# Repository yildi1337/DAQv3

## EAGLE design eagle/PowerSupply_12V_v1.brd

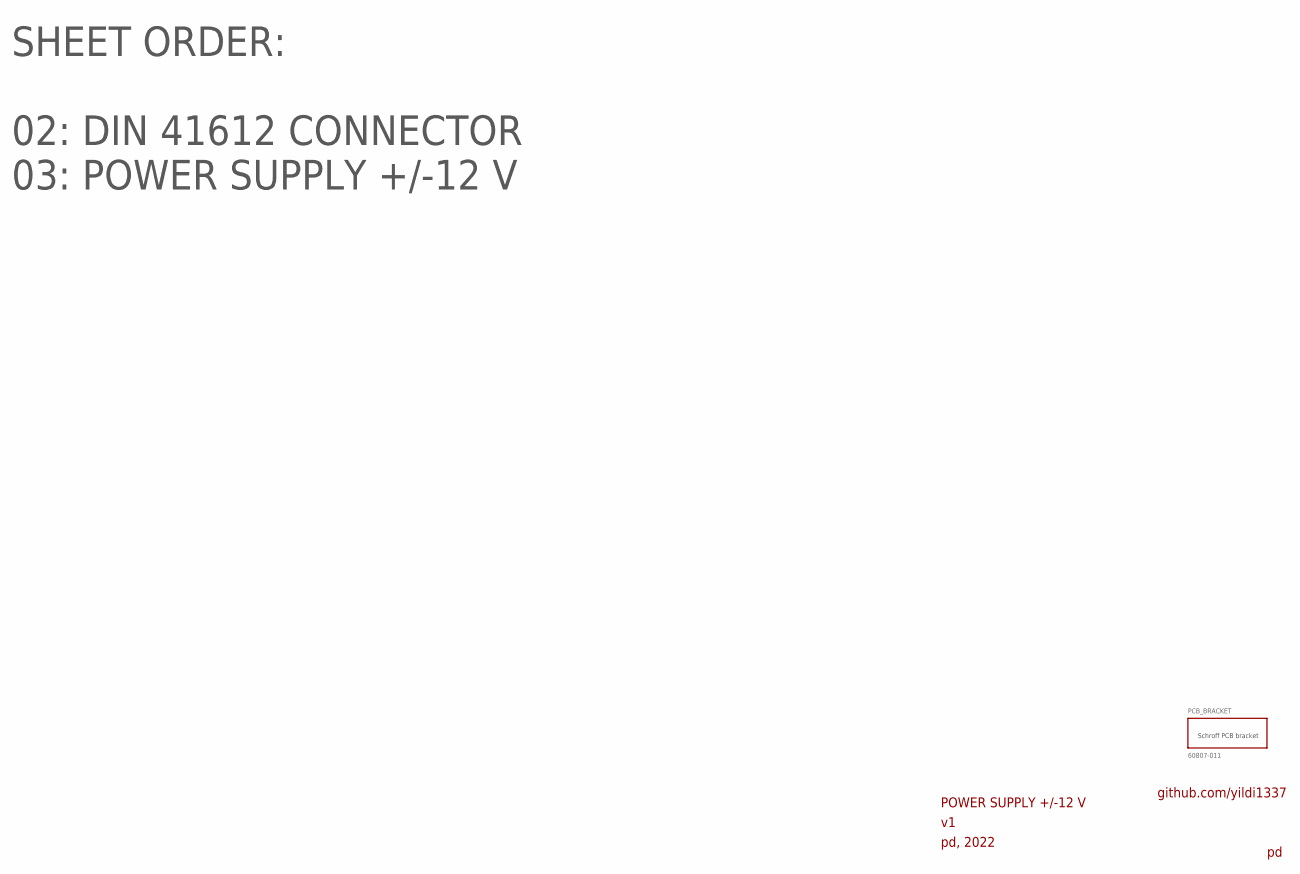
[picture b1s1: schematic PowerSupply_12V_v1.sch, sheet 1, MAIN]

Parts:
PCB_BRACKET: 60807-011

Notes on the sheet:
POWER SUPPLY +/-12 V
pd, 2022
github.com/yildi1337
SHEET ORDER: 02: DIN 41612 CONNECTOR 03: POWER SUPPLY +/-12 V

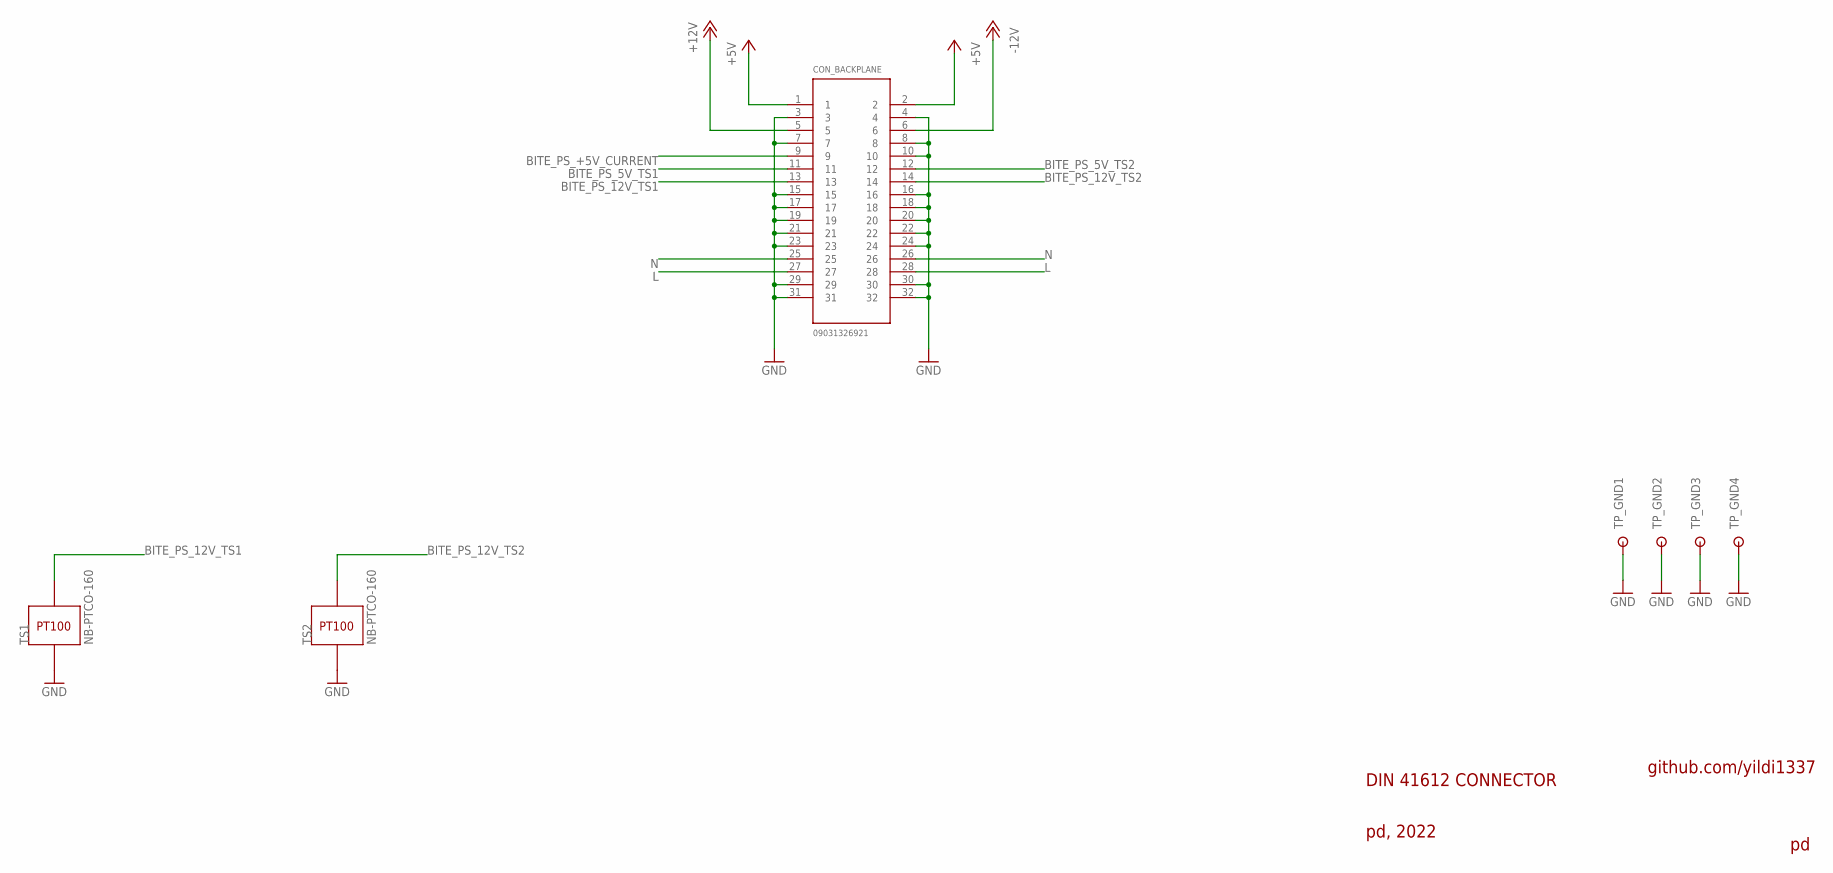
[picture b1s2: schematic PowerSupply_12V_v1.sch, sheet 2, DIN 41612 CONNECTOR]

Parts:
CON_BACKPLANE: 09031326921
TP_GND1, TP_GND2, TP_GND3, TP_GND4: RSPRO-1MM-TERMINAL-POST-2622034
TS1, TS2: NB-PTCO-160

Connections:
+5V: CON_BACKPLANE.1, CON_BACKPLANE.2
+12V: CON_BACKPLANE.5; also elsewhere on the board
-12V: CON_BACKPLANE.6; also elsewhere on the board
BITE_PS_5V_TS1: CON_BACKPLANE.11
BITE_PS_5V_TS2: CON_BACKPLANE.12
BITE_PS_12V_TS1: CON_BACKPLANE.13, TS1.1
BITE_PS_12V_TS2: CON_BACKPLANE.14, TS2.1
BITE_PS_+5V_CURRENT: CON_BACKPLANE.9
GND: CON_BACKPLANE.3, CON_BACKPLANE.4, CON_BACKPLANE.7, CON_BACKPLANE.8, CON_BACKPLANE.10, CON_BACKPLANE.15, CON_BACKPLANE.16, CON_BACKPLANE.17, CON_BACKPLANE.18, CON_BACKPLANE.19, CON_BACKPLANE.20, CON_BACKPLANE.21, CON_BACKPLANE.22, CON_BACKPLANE.23, CON_BACKPLANE.24, CON_BACKPLANE.29, CON_BACKPLANE.30, CON_BACKPLANE.31, CON_BACKPLANE.32, TP_GND1.P$1, TP_GND2.P$1, TP_GND3.P$1, TP_GND4.P$1, TS1.2, TS2.2; also elsewhere on the board
L: CON_BACKPLANE.27, CON_BACKPLANE.28; also elsewhere on the board
N: CON_BACKPLANE.25, CON_BACKPLANE.26; also elsewhere on the board

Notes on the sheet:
DIN 41612 CONNECTOR
pd, 2022
github.com/yildi1337

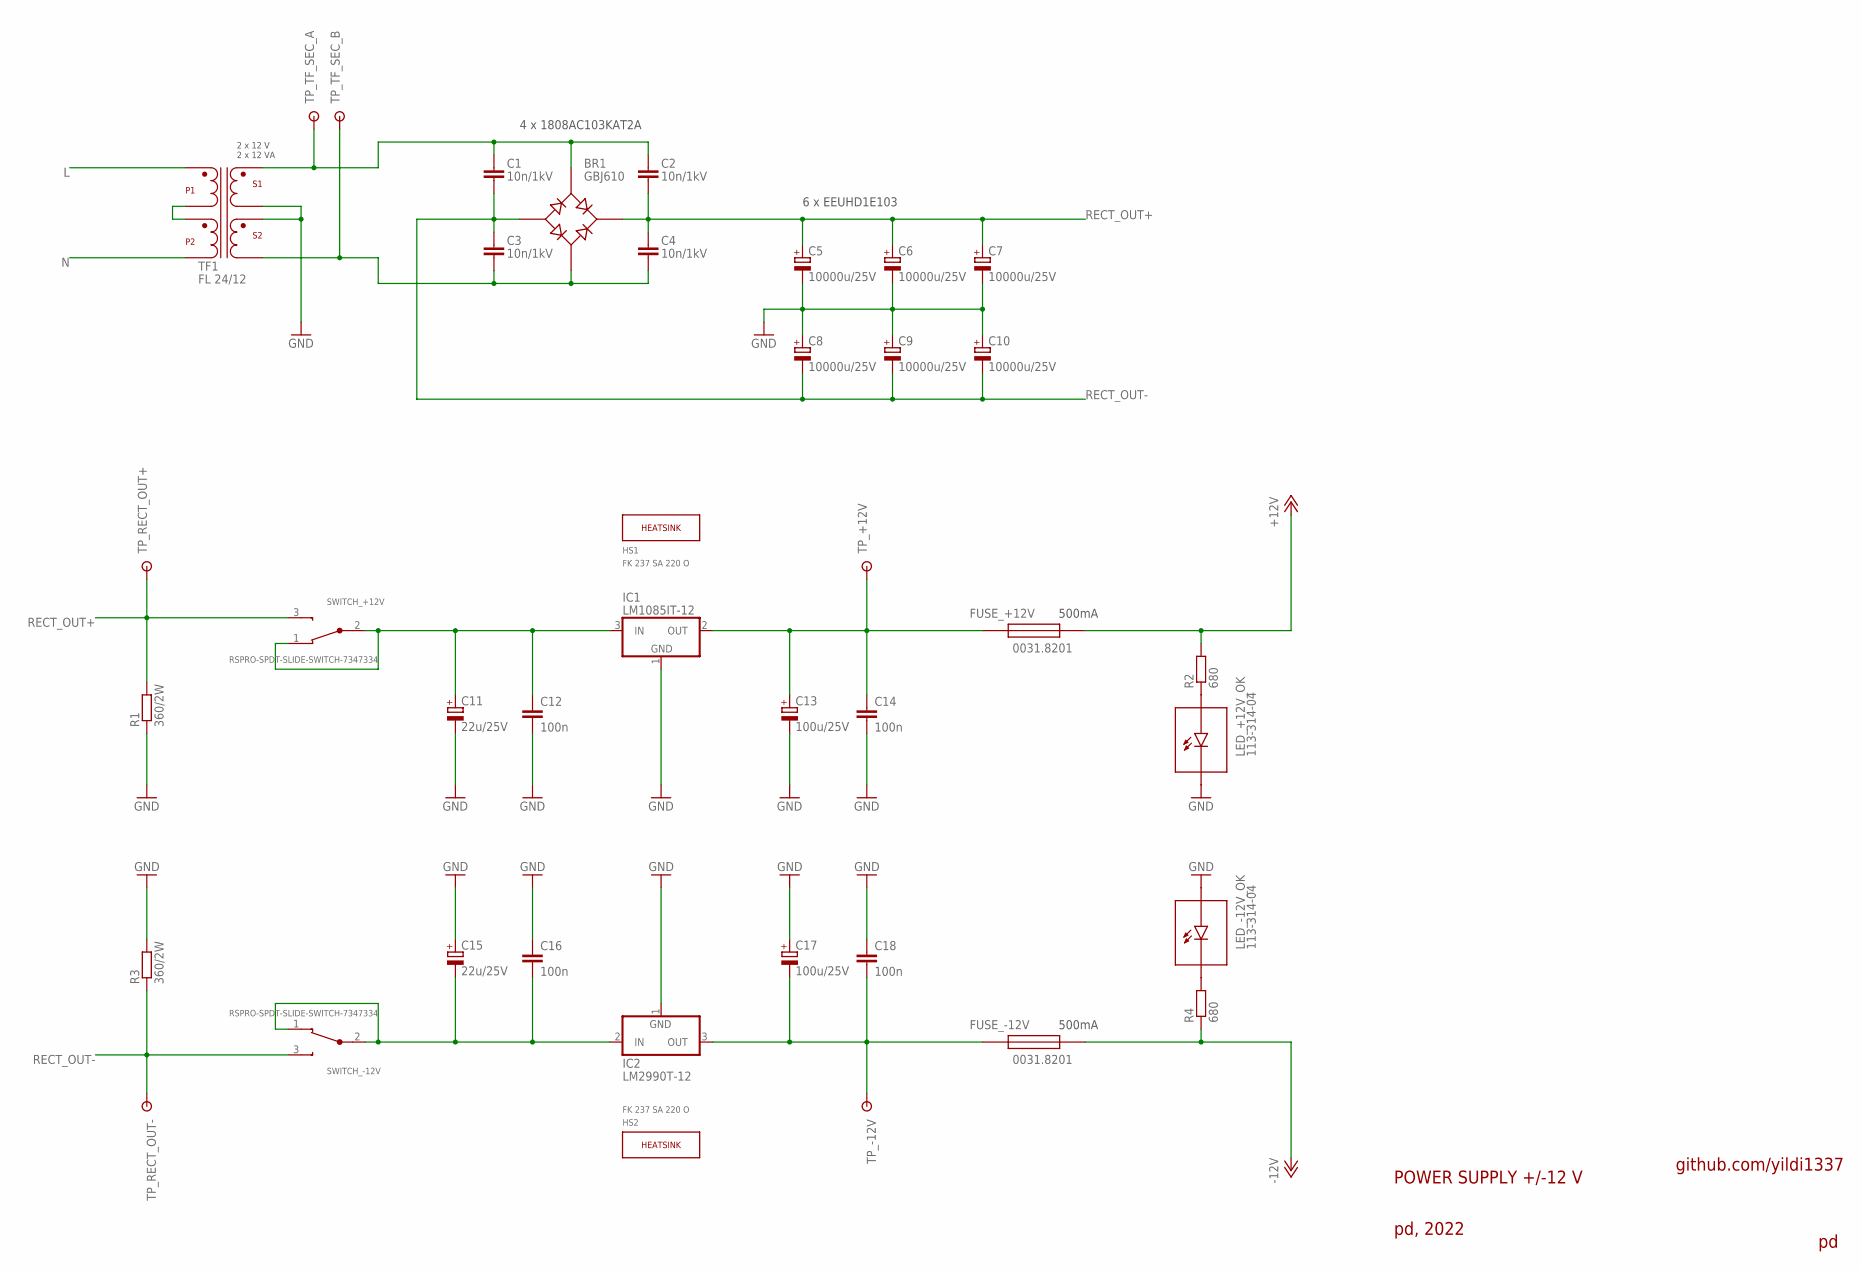
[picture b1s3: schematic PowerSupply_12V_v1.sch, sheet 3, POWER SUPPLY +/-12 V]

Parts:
BR1: GBJ610
C1, C2, C3, C4: 10n/1kV; C1808
C5, C6, C7, C8, C9, C10: 10000u/25V; EEUHD1E103
C11, C15: 22u/25V; 153CLV-0505
C12, C14, C16, C18: 100n; C0603
C13, C17: 100u/25V; 153CLV-0810
FUSE_+12V: 0031.8201
FUSE_-12V: 0031.8201
HS1, HS2: FK 237 SA 220 O; FK_237_SA_220_O
IC1: LM1085IT-12
IC2: LM2990T-12
LED_+12V_OK: 113-314-04
LED_-12V_OK: 113-314-04
R1, R3: 360/2W; R2010
R2, R4: 680; R0603
SWITCH_+12V: RSPRO-SPDT-SLIDE-SWITCH-7347334
SWITCH_-12V: RSPRO-SPDT-SLIDE-SWITCH-7347334
TF1: FL 24/12; FL_24-12
TP_+12V: RSPRO-1MM-TERMINAL-POST-2622034
TP_-12V: RSPRO-1MM-TERMINAL-POST-2622034
TP_RECT_OUT+: RSPRO-1MM-TERMINAL-POST-2622034
TP_RECT_OUT-: RSPRO-1MM-TERMINAL-POST-2622034
TP_TF_SEC_A: RSPRO-1MM-TERMINAL-POST-2622034
TP_TF_SEC_B: RSPRO-1MM-TERMINAL-POST-2622034

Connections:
+12V: FUSE_+12V.2, R2.2; also elsewhere on the board
-12V: FUSE_-12V.2, R4.1; also elsewhere on the board
GND: C5.-, C6.-, C7.-, C8.+, C9.+, C10.+, C11.-, C12.2, C13.-, C14.2, C15.+, C16.1, C17.+, C18.1, IC1.1 (GND), IC2.1 (GND), LED_+12V_OK.- (C), LED_-12V_OK.+ (A), R1.1, R3.2, TF1.S1B, TF1.S2A; also elsewhere on the board
L: TF1.P1A; also elsewhere on the board
N: TF1.P2B; also elsewhere on the board
unnamed: C15.-, C16.2, IC2.2 (IN), SWITCH_-12V.1 (NC), SWITCH_-12V.2 (COM)
unnamed: LED_-12V_OK.- (C), R4.2
unnamed: C17.-, C18.2, FUSE_-12V.1, IC2.3 (OUT), TP_-12V.P$1
unnamed: TF1.P1B, TF1.P2A
unnamed: BR1.L, C1.1, C2.1, TF1.S1A, TP_TF_SEC_A.P$1
unnamed: LED_+12V_OK.+ (A), R2.1
unnamed: C13.+, C14.1, FUSE_+12V.1, IC1.2 (OUT), TP_+12V.P$1
unnamed: BR1.N, C3.2, C4.2, TF1.S2B, TP_TF_SEC_B.P$1
unnamed: C11.+, C12.1, IC1.3 (IN), SWITCH_+12V.1 (NC), SWITCH_+12V.2 (COM)
RECT_OUT+: BR1.+, C2.2, C4.1, C5.+, C6.+, C7.+, R1.2, SWITCH_+12V.3 (NO), TP_RECT_OUT+.P$1
RECT_OUT-: BR1.-, C1.2, C3.1, C8.-, C9.-, C10.-, R3.1, SWITCH_-12V.3 (NO), TP_RECT_OUT-.P$1

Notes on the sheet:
POWER SUPPLY +/-12 V
pd, 2022
github.com/yildi1337
4 x 1808AC103KAT2A
6 x EEUHD1E103
500mA

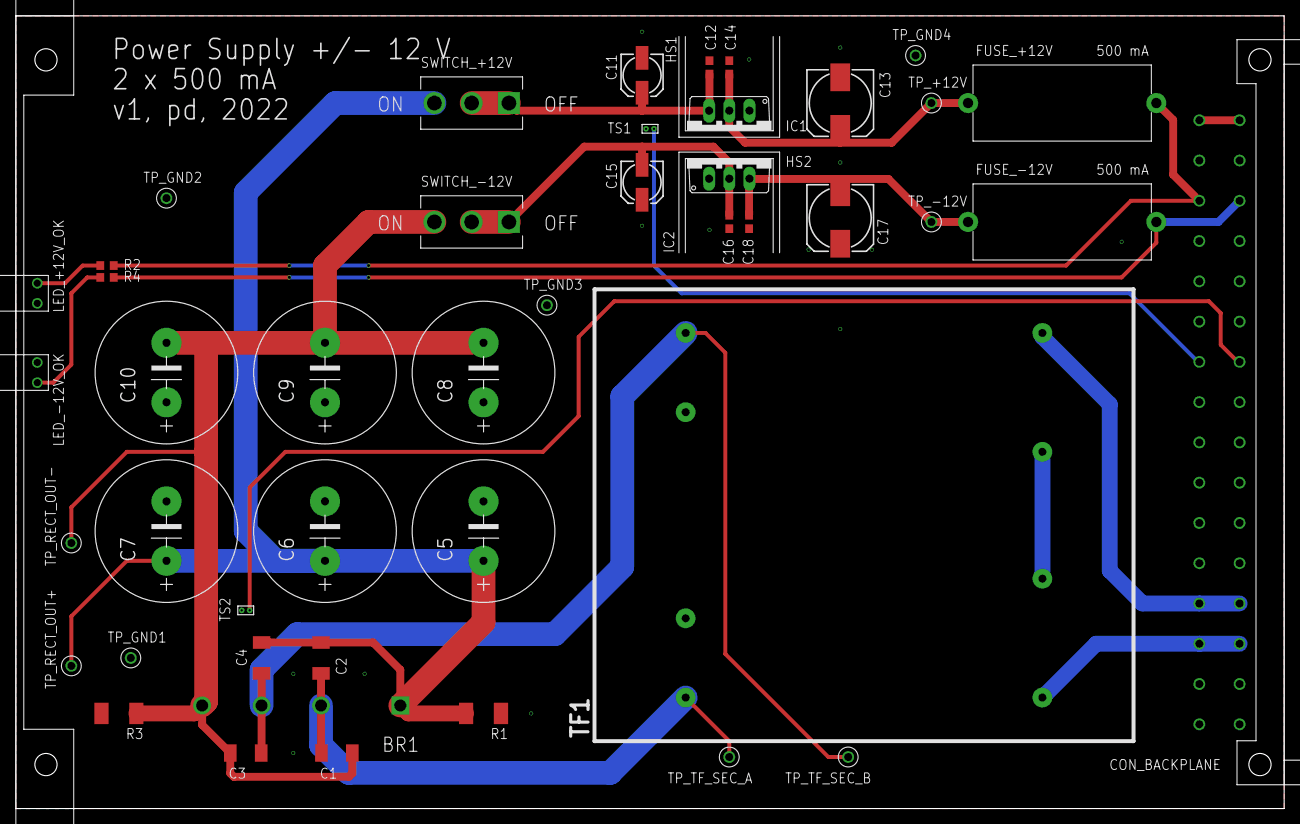
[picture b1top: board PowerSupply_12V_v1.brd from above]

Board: 2 copper layers, 160.0 x 100.0 mm, 48 parts (0 on the bottom side), 19 nets.
